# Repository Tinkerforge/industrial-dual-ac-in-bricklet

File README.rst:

Industrial Dual AC In Bricklet
==============================

**This Bricklet is currently in development.**

This repository contains the firmware source code and the hardware design
files. The documentation generator configs can be found at
https://github.com/Tinkerforge/generators

Repository Content
------------------

software/:
 * examples/: Examples for all supported languages
 * build/: Compiled files
 * src/: Source code of firmware
 * Makefile: Makefile to build project

hardware/:
 * Contains KiCad project files and additionally schematics as PDF

datasheets/:
 * Contains datasheets for sensors and complex ICs that are used

Hardware
--------

The hardware is designed with the open source EDA Suite KiCad
(http://www.kicad.org). Before you are able to open the files,
you have to install the Tinkerforge kicad-libraries
(https://github.com/Tinkerforge/kicad-libraries). You can either clone
them directly in hardware/ or clone them in a separate folder and
symlink them into hardware/
(ln -s kicad_path/kicad-libraries project_path/hardware). After that you
can open the .pro file in hardware/ with KiCad and from there view and
modify the schematics and the PCB layout.

Software
--------

If you want to do your own Brick/Bricklet firmware development we highly
recommend that you use our build environment setup script and read the
tutorial (https://www.tinkerforge.com/en/doc/Tutorials/Tutorial_Build_Environment/Tutorial.html).

To compile the C code we recommend you to install the newest GNU Arm Embedded
Toolchain (https://launchpad.net/gcc-arm-embedded/+download).
You also need to install bricklib2 (https://github.com/Tinkerforge/bricklib2).

You can either clone it directly in software/src/ or clone it in a
separate folder and symlink it into software/src/
(ln -s bricklib_path/bricklib2 project_path/software/src/). Finally make sure to
have CMake installed (http://www.cmake.org/cmake/resources/software.html).

After that you can build the firmware by invoking make in software/.
The firmware (.zbin) can then be found in software/build/ and uploaded
with brickv (click button "Flashing" on start screen).

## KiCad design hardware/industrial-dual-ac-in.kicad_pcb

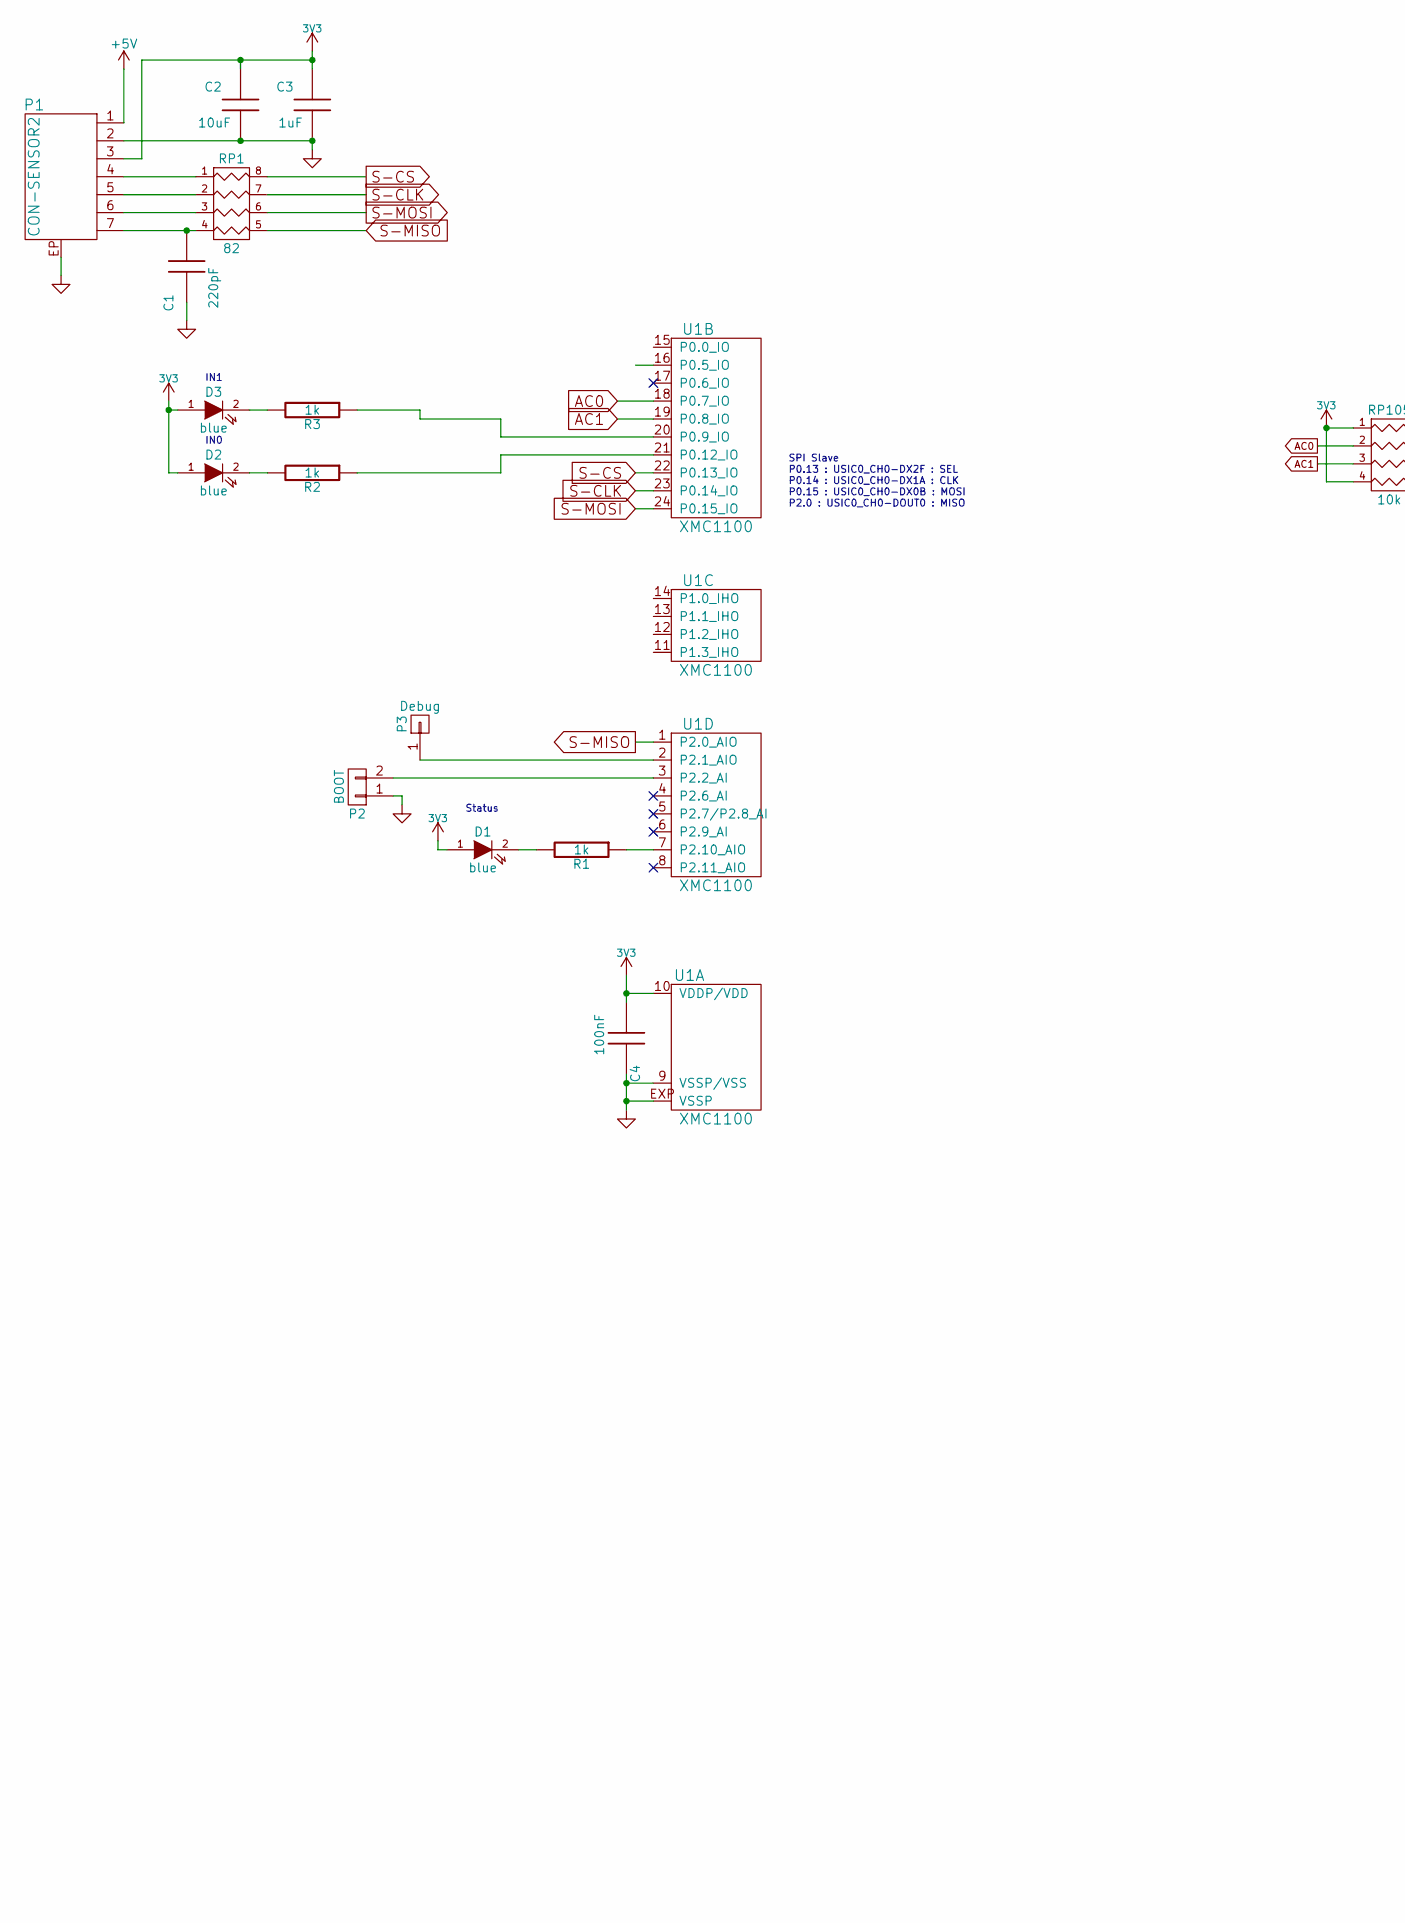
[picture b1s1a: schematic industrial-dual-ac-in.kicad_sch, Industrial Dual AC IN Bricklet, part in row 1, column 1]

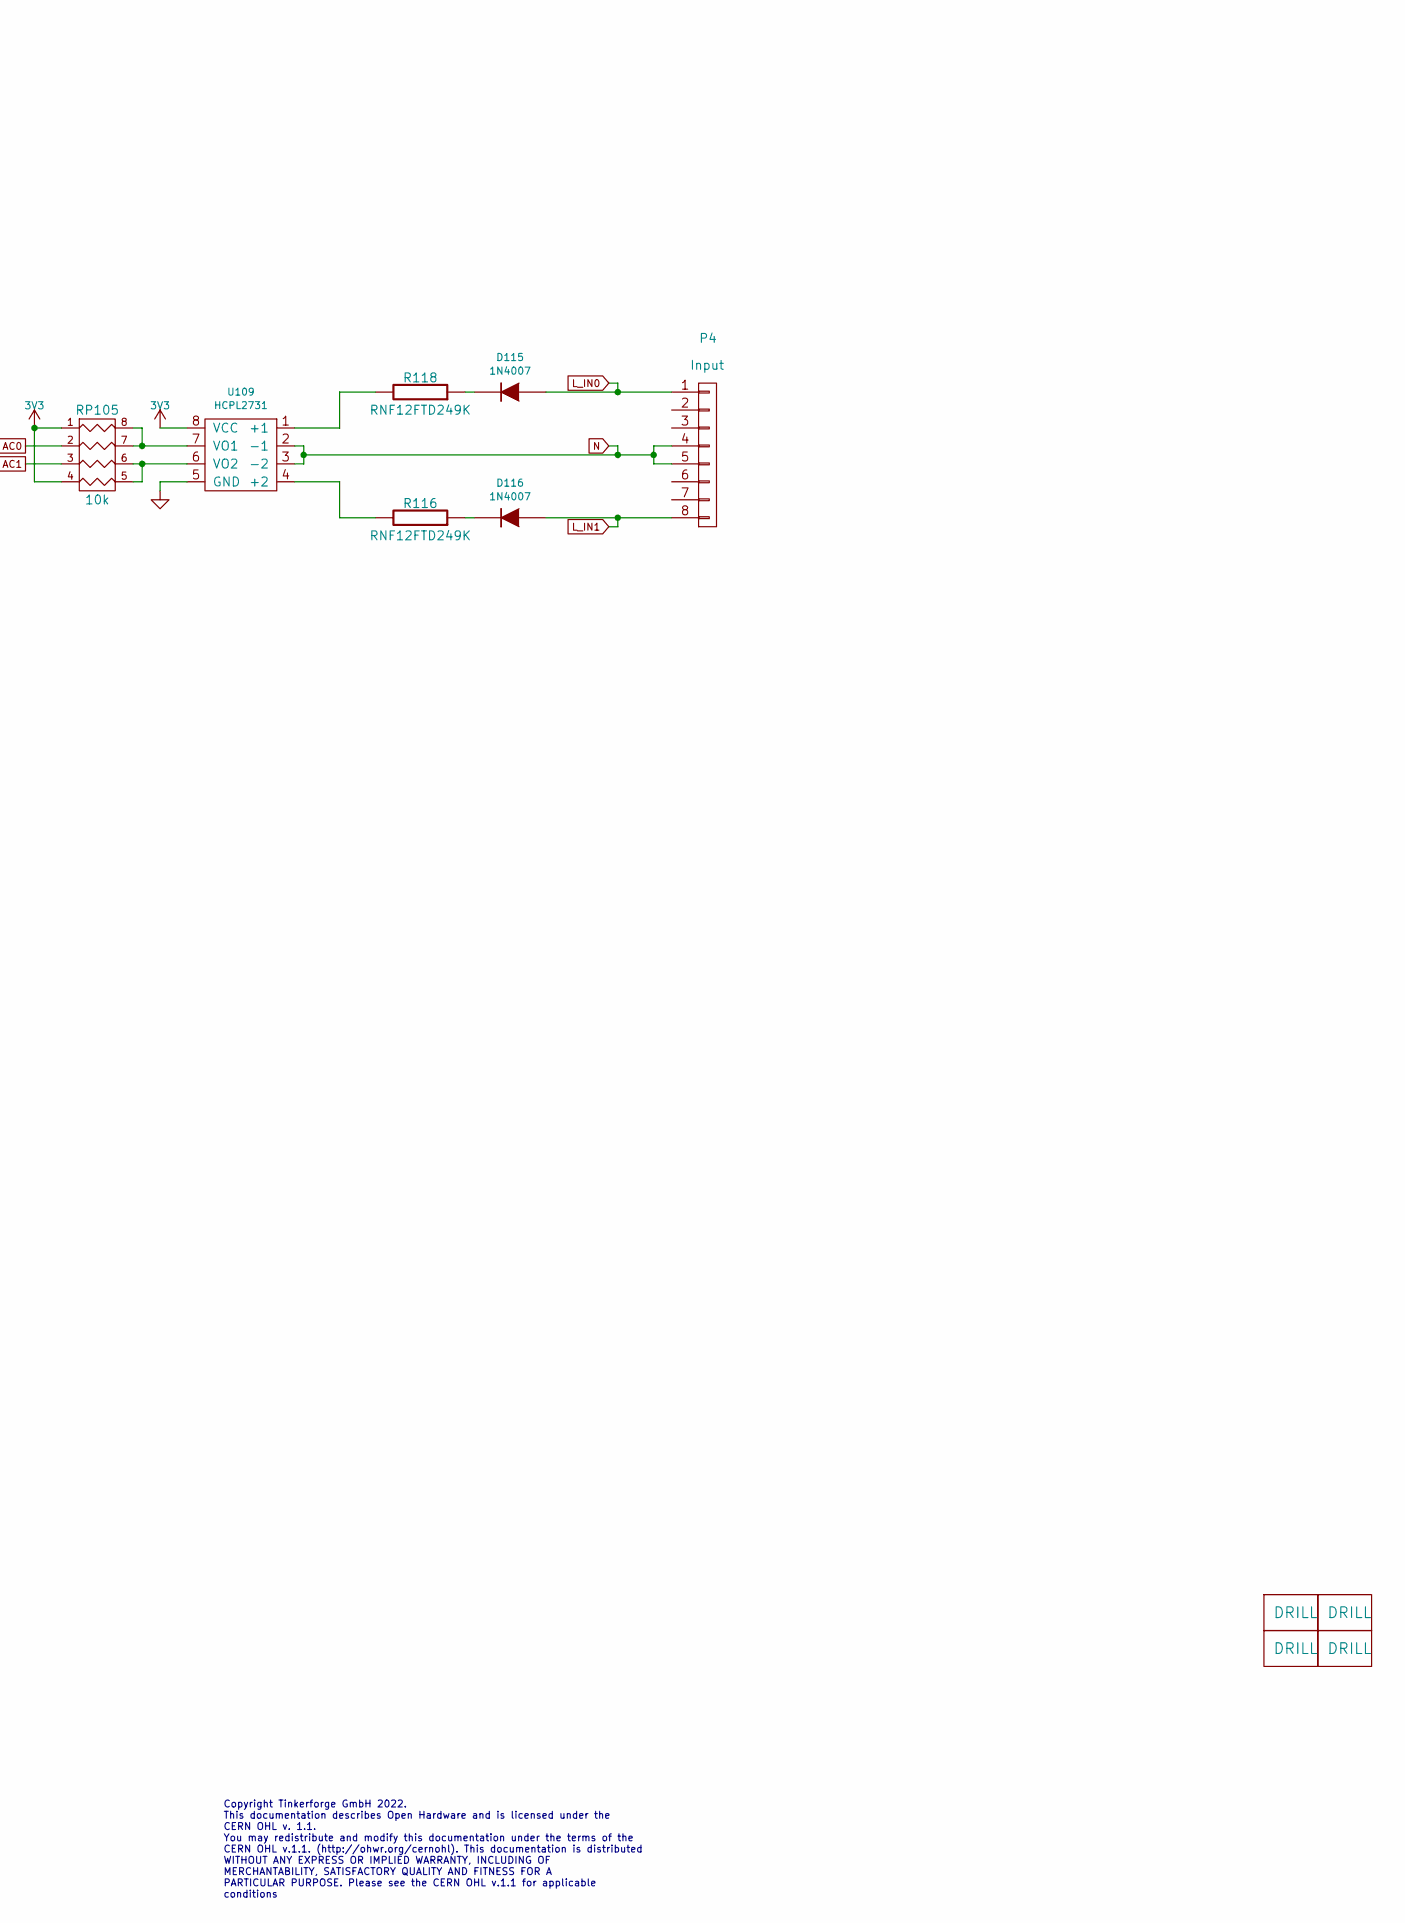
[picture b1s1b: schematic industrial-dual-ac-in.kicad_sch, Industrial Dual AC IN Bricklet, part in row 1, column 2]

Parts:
C1: 220pF; C0402F
C2: 10uF; C0805E
C3: 1uF; C0603F
C4: 100nF; C0603F
D1, D2, D3: blue; D0603E
D115, D116: 1N4007; DO-41
Drill1, Drill2, Drill3, Drill4: DRILL; DRILL_NP
P1: CON-SENSOR2
P2: BOOT; SolderJumper
P3: Debug; DEBUG_PAD
P4: Input; OQ_8P_230V
R1, R2, R3: 1k; R0603F
R116, R118: RNF12FTD249K; RNF12-2
RP1: 82; 4X0402
RP105: 10k; 4X0603
U1: XMC1100; QFN24-4x4mm-0.5mm
U109: HCPL2731; DIP-8

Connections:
3V3: C2.2, C3.2, C4.1, D1.1 (A), D2.1 (A), D3.1 (A), P1.3, RP105.1, RP105.4, U1.10 (VDDP/VDD), U109.8 (VCC)
+5V: P1.1
AC0: RP105.2, U1.18 (P0.7_IO)
AC1: RP105.3, U1.19 (P0.8_IO)
GND: C1.1, C2.1, C3.1, C4.2, P1.2, P1.EP, P2.1, U1.9 (VSSP/VSS), U1.EXP (VSSP), U109.5 (GND)
L_IN0: D115.1 (A), P4.1
L_IN1: D116.1 (A), P4.8
N: P4.4, P4.5, U109.2 (-1), U109.3 (-2)
unnamed: D1.2 (K), R1.2
unnamed: D2.2 (K), R2.2
unnamed: D3.2 (K), R3.2
unnamed: D115.2 (K), R118.1
unnamed: D116.2 (K), R116.1
unnamed: P2.2, U1.3 (P2.2_AI)
unnamed: P3.1, U1.2 (P2.1_AIO)
unnamed: P1.4, RP1.1
unnamed: P1.5, RP1.2
unnamed: P1.6, RP1.3
unnamed: C1.2, P1.7, RP1.4
unnamed: RP105.7 (R2), RP105.8 (R1), U109.7 (VO1)
unnamed: RP105.5 (R4), RP105.6 (R3), U109.6 (VO2)
unnamed: R3.1, U1.20 (P0.9_IO)
unnamed: R2.1, U1.21 (P0.12_IO)
unnamed: R1.1, U1.7 (P2.10_AIO)
unnamed: R118.2, U109.1 (+1)
unnamed: R116.2, U109.4 (+2)
S-CLK: RP1.7 (R2), U1.23 (P0.14_IO)
S-CS: RP1.8 (R1), U1.22 (P0.13_IO)
S-MISO: RP1.5 (R4), U1.1 (P2.0_AIO)
S-MOSI: RP1.6 (R3), U1.24 (P0.15_IO)

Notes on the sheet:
SPI Slave P0.13 : USIC0_CH0-DX2F : SEL P0.14 : USIC0_CH0-DX1A : CLK P0.15 : USIC0_CH0-DX0B : MOSI P2.0 : USIC0_CH0-DOUT0 : MISO
Status
IN0
IN1
Copyright Tinkerforge GmbH 2022. This documentation describes Open Hardware and is licensed under the CERN OHL v. 1.1. You may redistribute and modify this documentation under the terms of the CERN OHL v.1.1. (http://ohwr.org/cernohl). This documentation is distributed WITHOUT ANY EXPRESS OR IMPLIE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

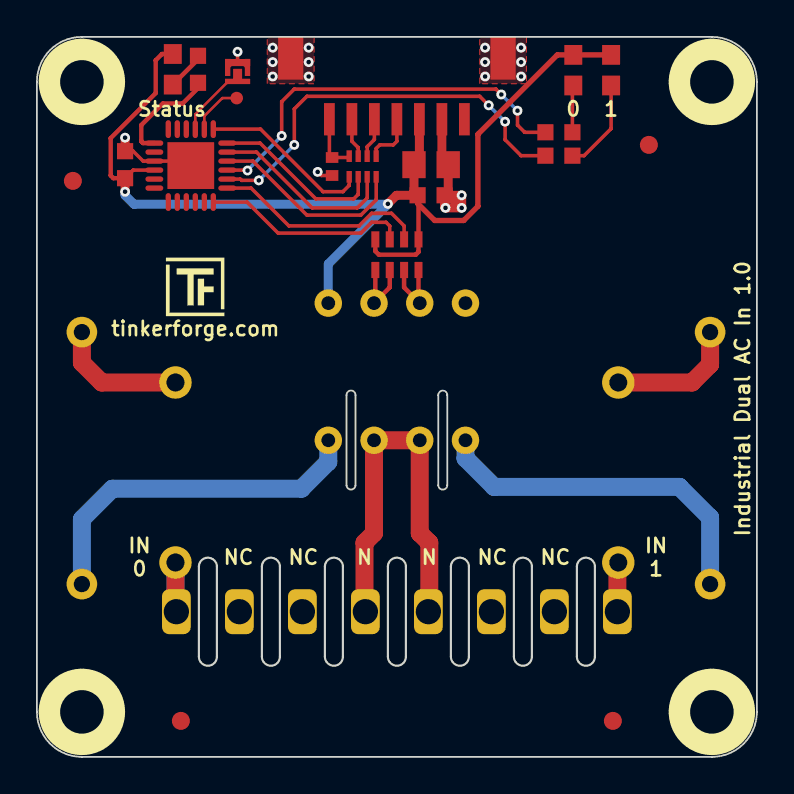
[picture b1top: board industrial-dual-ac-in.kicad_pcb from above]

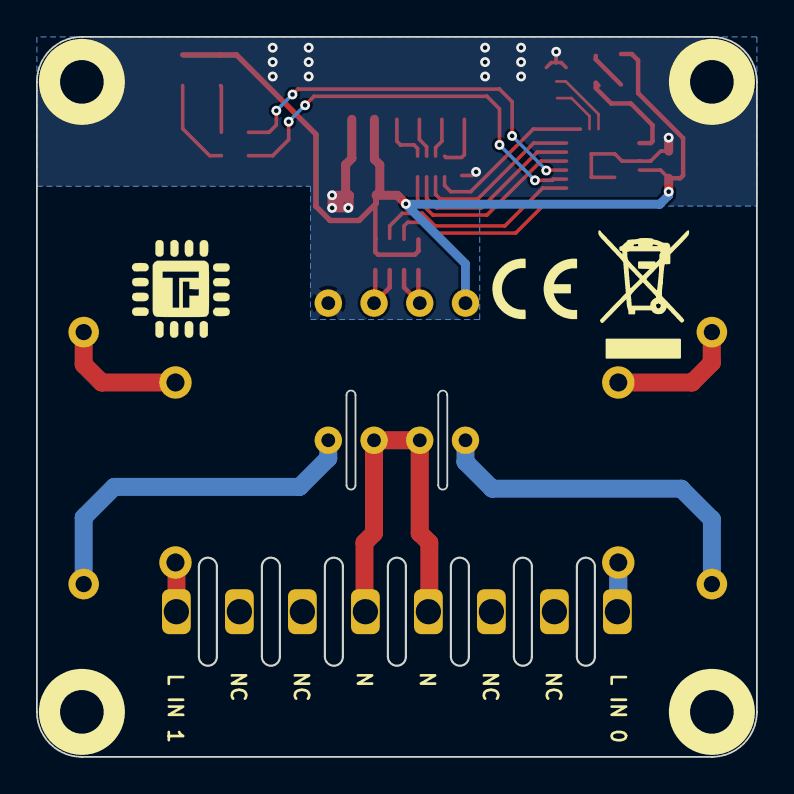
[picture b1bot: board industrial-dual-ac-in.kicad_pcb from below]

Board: 2 copper layers, 40.0 x 40.0 mm, 32 parts (2 on the bottom side), 29 nets.

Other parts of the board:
Fiducial_Mark: VAL**; Fiducial_Mark
Fiducial_Mark#2, Fiducial_Mark#3, Fiducial_Mark#4: VAL**; Fiducial_Mark
VAL: WEEE_7mm
VAL#2: CE_5mm

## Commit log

2022-11-16 ready for prototype
2022-11-16 more clearance for screwholes
2022-11-16 switched debug an boot pin
2022-11-28 added fiducial mark
2022-11-28 updated mounting holes
2023-02-08 Add Industrial Dual AC In Bricklet firmware
2023-05-12 Add HCPL2731 datasheet
2024-02-15 add schematic, update project
2025-10-04 Fix compatibility with new Docker build image (GCC 14.2.1)

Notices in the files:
hardware/industrial-dual-ac-in.kicad_pcb:
Licensed under CERN OHL v.1.1
Copyright (©) 2022, T.Schneidermann
